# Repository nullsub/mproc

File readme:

MPROC is a cpu built out of 74xx logic-gates.

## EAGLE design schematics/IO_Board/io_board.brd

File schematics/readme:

eagle is used for the schematics

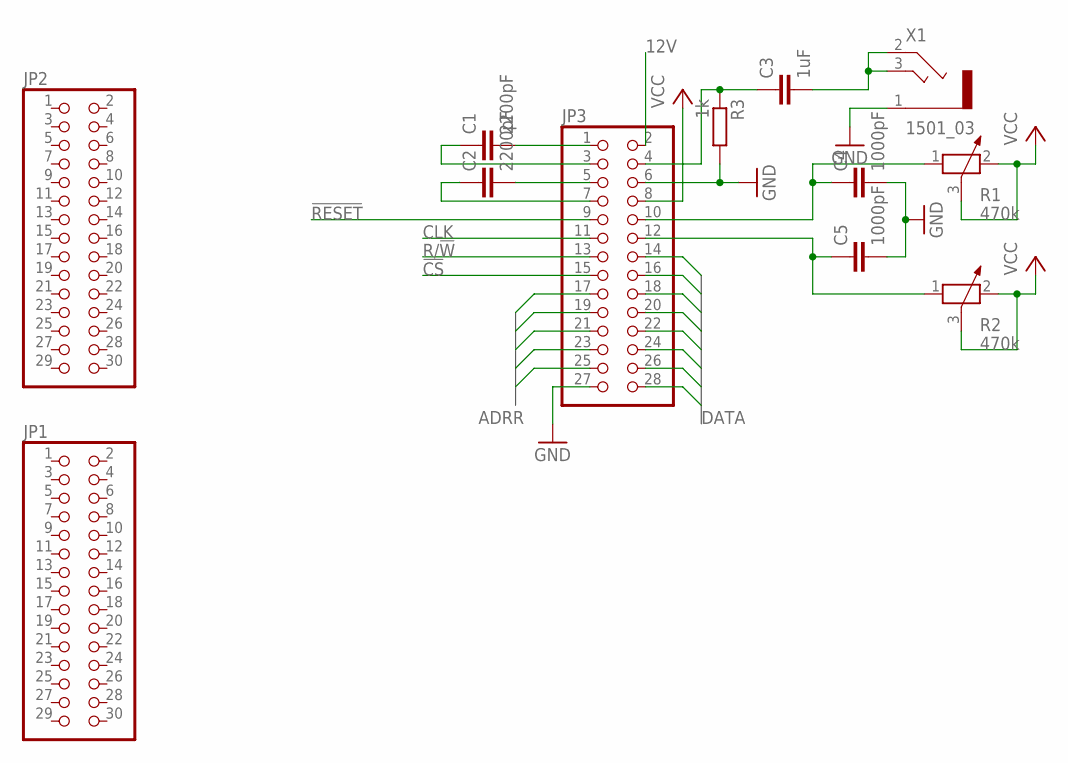
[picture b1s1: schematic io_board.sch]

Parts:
C1, C2: 2200pF; C1206
C3: 1uF; C1206
C4, C5: 1000pF; C1206
JP1, JP2: PINHD-2X15; 2X15
JP3: PINHD-2X14; 2X14
R1, R2: 470k; PT-10
R3: 1k; R0805
X1: 1501_03

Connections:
12V: JP3.2
!CS: JP3.15
!RESET: JP3.9
CLK: JP3.11
GND: C4.2, C5.2, JP3.6, JP3.27, R3.2, X1.1
unnamed: C4.1, JP3.10, R1.1
unnamed: C1.2, JP3.1
unnamed: C1.1, JP3.3
unnamed: C5.1, JP3.12, R2.1
unnamed: C2.2, JP3.5
unnamed: C2.1, JP3.7
unnamed: C3.2, X1.2, X1.3
unnamed: C3.1, JP3.4, R3.1
R/!W: JP3.13
VCC: JP3.8, R1.2, R1.3, R2.2, R2.3

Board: 2 copper layers, 12 parts (0 on the bottom side), 10 nets, no tracks yet.

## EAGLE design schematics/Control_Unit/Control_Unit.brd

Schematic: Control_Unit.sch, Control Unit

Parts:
IC1, IC8, IC48, IC49, IC55, IC56, IC65, IC68, IC70, IC71, IC94, IC96, IC112: 74HCT32N; DIL14
IC2, IC10, IC20, IC24, IC30, IC40, IC52, IC59, IC63, IC72, IC78, IC88, IC89, IC92, IC99, IC100, IC108, IC126, IC130: 74HCT08N; DIL14
IC3, IC4, IC15, IC16, IC22, IC23, IC31, IC32, IC37, IC38, IC42, IC43, IC46, IC47, IC50, IC51: 74HC151N; DIL16
IC5, IC18, IC26, IC33, IC41, IC45, IC73, IC79, IC81, IC85: 74HCT374N; DIL20
IC6, IC7, IC28, IC77, IC82, IC83, IC87, IC90, IC91, IC95: 74AC08N; DIL14
IC9: 74AC157N; DIL16
IC11, IC12, IC13, IC21, IC27, IC34: 74ACT157N; DIL16
IC14, IC67, IC86, IC129: 74HCT04N; DIL14
IC17, IC57, IC58, IC60, IC61, IC64, IC69, IC74, IC75, IC80, IC93, IC97, IC102, IC106: 74HC193N; DIL16
IC19, IC29, IC39, IC44: 74ACT02N; DIL14
IC25: 74AC86N; DIL14
IC35, IC36, IC101, IC103: 74HC373N; DIL20
IC53, IC54, IC105, IC131: 74HC74N; DIL14
JP1, JP2: PINHD-2X15; 2X15
JP3, JP4, JP5: PINHD-2X20; 2X20

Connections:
!CLR_CARRY_BIT: IC131.1 (CLR), JP4.12
!ENABLE_REG_OUTPUT: IC112.1 (I0), IC112.5 (I1), IC112.11 (O)
!IR_DATA_OUT_7: IC59.10 (I1), IC86.10 (O), IC99.10 (I1)
!OPCODE_5: IC14.6 (O), IC28.2 (I1), IC28.5 (I1)
!REGISTER_RESET: IC17.14 (CLR), IC57.14 (CLR), IC58.14 (CLR), IC60.14 (CLR), IC61.14 (CLR), IC64.14 (CLR), IC69.14 (CLR), IC74.14 (CLR), IC75.14 (CLR), IC80.14 (CLR), IC93.14 (CLR), IC97.14 (CLR), IC102.14 (CLR), IC106.14 (CLR), JP4.8
!RING_CNTR_RESET: IC53.4 (PRE), IC53.13 (CLR), IC54.1 (CLR), IC54.13 (CLR), IC105.1 (CLR), IC105.13 (CLR), JP4.10
!SET_CARRY_BIT: IC131.4 (PRE), JP4.14
!TWO_BYTE_CMD: IC14.11 (I), IC89.10 (I1), IC96.8 (O)
ADRR_0: IC13.4 (1Y), JP1.1
ADRR_1: IC13.7 (2Y), JP1.3
ADRR_2: IC13.9 (3Y), JP1.5
ADRR_3: IC13.12 (4Y), JP1.7
ADRR_4: IC21.4 (1Y), JP1.9
ADRR_5: IC21.7 (2Y), JP1.11
ADRR_6: IC21.9 (3Y), JP1.13
ADRR_7: IC21.12 (4Y), JP1.15
ADRR_8: IC27.4 (1Y), JP1.17
ADRR_9: IC27.7 (2Y), JP1.19
ADRR_10: IC27.9 (3Y), JP1.21
ADRR_11: IC27.12 (4Y), JP1.23
ADRR_12: IC34.4 (1Y), JP1.25
ADRR_13: IC34.7 (2Y), JP1.27
ADRR_14: IC34.9 (3Y), JP1.29
ADRR_15: IC34.12 (4Y), IC67.5 (I), IC68.9 (I0)
ALU_CARRY_BIT: IC78.12 (I0), IC89.4 (I0), IC131.5 (Q), JP4.16
ALU_CARRY_IN: IC89.6 (O), JP5.34
ALU_CARRY_OUT: IC72.5 (I1), IC99.9 (I0), IC131.2 (D), JP5.32
ALU_NR1_ENABLE_ALU: IC49.9 (I0), IC70.1 (I0), IC77.3 (O)
ALU_NR1_ENABLE_JMP_O: IC49.10 (I1), IC59.8 (O)
ALU_NR2_ENABLE_ALU: IC49.12 (I0), IC70.2 (I1), IC77.6 (O)
ALU_NR2_ENABLE_JMP_O: IC49.13 (I1), IC108.8 (O)
ALU_NR3_ENABLE_ALU: IC70.4 (I0), IC77.8 (O), JP5.26
ALU_NR4_ENABLE_ALU: IC70.5 (I1), IC77.11 (O), JP5.24
ALU_OUTPUT_ENABLE/FILL_PC_L_JMP_O: IC40.3 (O), IC49.2 (I1), IC56.12 (I0)
CARRY&&!IR_DATA: IC88.12 (I0), IC99.8 (O)
CARRY&&IR_DATA: IC72.6 (O), IC88.4 (I0)
CLR_NOT_CS/CLR_NOT_WE_PUSH: IC19.8 (I0), IC67.1 (I), IC126.6 (O)
CLR_NOT_OE/CLR_NOT_CS/PC_COUNT_UP_CYCL_2: IC53.9 (Q), IC55.4 (I0), IC55.12 (I0), JP4.28
CLR_NOT_OE/CLR_NOT_CS_POP/FILL_REGISTER_POP: IC19.9 (I1), IC96.4 (I0), IC100.6 (O), JP2.4
CLR_NOT_OE/PC_COUNT_UP/CLR_NOT_CS_CYCL_1: IC53.5 (Q), IC55.5 (I1), IC89.9 (I0), IC89.12 (I0), JP4.26
CYCLE1/CYLCE2: IC19.6 (I1), IC39.11 (I0), IC55.6 (O), IC68.4 (I0)
DATA0: IC5.3 (1D), IC17.15 (A), IC18.3 (1D), IC26.3 (1D), IC33.3 (1D), IC35.2 (1Q), IC36.2 (1Q), IC41.3 (1D), IC45.3 (1D), IC57.15 (A), IC60.15 (A), IC69.15 (A), IC73.3 (1D), IC79.3 (1D), IC81.3 (1D), IC85.3 (1D), IC101.2 (1Q), IC103.3 (1D), JP1.2, JP5.23
DATA1: IC5.4 (2D), IC17.1 (B), IC18.4 (2D), IC26.4 (2D), IC33.4 (2D), IC35.5 (2Q), IC36.5 (2Q), IC41.4 (2D), IC45.4 (2D), IC57.1 (B), IC60.1 (B), IC69.1 (B), IC73.4 (2D), IC79.4 (2D), IC81.4 (2D), IC85.4 (2D), IC101.5 (2Q), IC103.4 (2D), JP1.4, JP5.25
DATA2: IC5.7 (3D), IC17.10 (C), IC18.7 (3D), IC26.7 (3D), IC33.7 (3D), IC35.6 (3Q), IC36.6 (3Q), IC41.7 (3D), IC45.7 (3D), IC57.10 (C), IC60.10 (C), IC69.10 (C), IC73.7 (3D), IC79.7 (3D), IC81.7 (3D), IC85.7 (3D), IC101.6 (3Q), IC103.7 (3D), JP1.6, JP5.27
DATA3: IC5.8 (4D), IC17.9 (D), IC18.8 (4D), IC26.8 (4D), IC33.8 (4D), IC35.9 (4Q), IC36.9 (4Q), IC41.8 (4D), IC45.8 (4D), IC57.9 (D), IC60.9 (D), IC69.9 (D), IC73.8 (4D), IC79.8 (4D), IC81.8 (4D), IC85.8 (4D), IC101.9 (4Q), IC103.8 (4D), JP1.8, JP5.29
DATA4: IC5.13 (5D), IC18.13 (5D), IC26.13 (5D), IC33.13 (5D), IC35.12 (5Q), IC36.12 (5Q), IC41.13 (5D), IC45.13 (5D), IC58.15 (A), IC61.15 (A), IC64.15 (A), IC73.13 (5D), IC74.15 (A), IC79.13 (5D), IC81.13 (5D), IC85.13 (5D), IC101.12 (5Q), IC103.13 (5D), JP1.10, JP5.31
DATA5: IC5.14 (6D), IC18.14 (6D), IC26.14 (6D), IC33.14 (6D), IC35.15 (6Q), IC36.15 (6Q), IC41.14 (6D), IC45.14 (6D), IC58.1 (B), IC61.1 (B), IC64.1 (B), IC73.14 (6D), IC74.1 (B), IC79.14 (6D), IC81.14 (6D), IC85.14 (6D), IC101.15 (6Q), IC103.14 (6D), JP1.12, JP5.33
DATA6: IC5.17 (7D), IC18.17 (7D), IC26.17 (7D), IC33.17 (7D), IC35.16 (7Q), IC36.16 (7Q), IC41.17 (7D), IC45.17 (7D), IC58.10 (C), IC61.10 (C), IC64.10 (C), IC73.17 (7D), IC74.10 (C), IC79.17 (7D), IC81.17 (7D), IC85.17 (7D), IC101.16 (7Q), IC103.17 (7D), JP1.14, JP5.35
DATA7: IC5.18 (8D), IC18.18 (8D), IC26.18 (8D), IC33.18 (8D), IC35.19 (8Q), IC36.19 (8Q), IC41.18 (8D), IC45.18 (8D), IC58.9 (D), IC61.9 (D), IC64.9 (D), IC73.18 (8D), IC74.9 (D), IC79.18 (8D), IC81.18 (8D), IC85.18 (8D), IC101.19 (8Q), IC103.18 (8D), JP1.16, JP5.37
DATA_BUS_ENABLE_LATCH: IC35.11 (ENC), IC59.3 (O)
DBUS_SELECTOR_TABLE_2: IC11.1 (!A!/B), IC55.8 (O)
ENABLE_ALU_OUTPUT: IC49.3 (O), IC67.11 (I), IC112.13 (I1)
ENABLE_ALU_OUTPUT/FILL_REGISTER_ALU: IC49.1 (I0), IC72.11 (O), IC112.10 (I1)
FDSGDFGFDSGFSDGFDGSDG: IC8.10 (I1), IC8.13 (I1), IC19.1 (O)
FILL_LR_H/COUNT_PC_DOWN_SAVE_LR: IC44.11 (I0), IC126.11 (O), IC129.9 (I)
FILL_LR_L/WRITE_PC_H_DBUS_SAVE_LR: IC44.8 (I0), IC65.13 (I1), IC92.6 (O)
FILL_PC_H_RET: IC56.4 (I0), IC126.3 (O)
FILL_PC_L/WRITE_LR_H_DBUS_RET: IC56.10 (I1), IC65.2 (I1), IC65.4 (I0), IC100.3 (O)
FILL_PTR_H_SET_PTR: IC39.6 (I1), IC88.8 (O)
FILL_PTR_L/WRITE_REGB_TO_DBUS_SET_PTR: IC1.13 (I1), IC39.3 (I1), IC92.3 (O)
FILL_REGISTER_MOV: IC108.3 (O), IC112.9 (I0)
FSDFAFSDFSFDDDDDDDDDDDDDDDDDDDDDDDDDDDDDDDD1: IC2.2 (I1), IC2.10 (I1), IC10.2 (I1), IC10.10 (I1), IC20.6 (O)
GND: IC1.7 (GND), IC2.7 (GND), IC3.7 (G), IC3.8 (GND), IC4.7 (G), IC4.8 (GND), IC5.1 (OC), IC5.10 (GND), IC6.7 (GND), IC7.7 (GND), IC8.7 (GND), IC9.8 (GND), IC9.15 (G), IC10.7 (GND), IC11.8 (GND), IC11.14 (4A), IC11.15 (G), IC12.3 (1B), IC12.8 (GND), IC12.15 (G), IC13.8 (GND), IC13.15 (G), IC14.7 (GND), IC15.7 (G), IC15.8 (GND), IC16.7 (G), IC16.8 (GND), IC17.8 (GND), IC18.1 (OC), IC18.10 (GND), IC19.7 (GND), IC20.7 (GND), IC21.8 (GND), IC21.15 (G), IC22.7 (G), IC22.8 (GND), IC23.7 (G), IC23.8 (GND), IC24.7 (GND), IC25.7 (GND), IC26.1 (OC), IC26.10 (GND), IC27.8 (GND), IC27.15 (G), IC28.7 (GND), IC29.7 (GND), IC30.7 (GND), IC31.7 (G), IC31.8 (GND), IC32.7 (G), IC32.8 (GND), IC33.1 (OC), IC33.10 (GND), IC34.8 (GND), IC34.15 (G), IC35.10 (GND), IC36.10 (GND), IC37.7 (G), IC37.8 (GND), IC38.7 (G), IC38.8 (GND), IC39.7 (GND), IC40.7 (GND), IC41.1 (OC), IC41.10 (GND), IC42.7 (G), IC42.8 (GND), IC43.7 (G), IC43.8 (GND), IC44.7 (GND), IC45.1 (OC), IC45.10 (GND), IC46.7 (G), IC46.8 (GND), IC47.7 (G), IC47.8 (GND), IC48.7 (GND), IC49.7 (GND), IC50.7 (G), IC50.8 (GND), IC51.7 (G), IC51.8 (GND), IC52.7 (GND), IC53.7 (GND), IC54.7 (GND), IC55.7 (GND), IC56.7 (GND), IC57.8 (GND), IC58.8 (GND), IC59.7 (GND), IC60.8 (GND), IC61.8 (GND), IC63.7 (GND), IC64.8 (GND), IC65.7 (GND), IC67.7 (GND), IC68.7 (GND), IC69.8 (GND), IC70.7 (GND), IC71.7 (GND), IC72.7 (GND), IC73.1 (OC), IC73.10 (GND), IC74.8 (GND), IC75.1 (B), IC75.8 (GND), IC75.9 (D), IC75.10 (C), IC75.15 (A), IC77.7 (GND), IC78.7 (GND), IC79.1 (OC), IC79.10 (GND), IC80.1 (B), IC80.8 (GND), IC80.9 (D), IC80.10 (C), IC80.15 (A), IC81.1 (OC), IC81.10 (GND), IC82.7 (GND), IC83.7 (GND), IC85.1 (OC), IC85.10 (GND), IC86.7 (GND), IC87.7 (GND), IC88.7 (GND), IC89.7 (GND), IC90.7 (GND), IC91.7 (GND), IC92.7 (GND), IC93.1 (B), IC93.8 (GND), IC93.9 (D), IC93.10 (C), IC93.15 (A), IC94.7 (GND), IC95.7 (GND), IC96.7 (GND), IC97.1 (B), IC97.8 (GND), IC97.9 (D), IC97.10 (C), IC97.15 (A), IC99.7 (GND), IC100.7 (GND), IC101.10 (GND), IC102.1 (B), IC102.8 (GND), IC102.9 (D), IC102.10 (C), IC102.15 (A), IC103.1 (OC), IC103.10 (GND), IC105.7 (GND), IC106.1 (B), IC106.8 (GND), IC106.9 (D), IC106.10 (C), IC106.15 (A), IC108.7 (GND), IC112.7 (GND), IC126.7 (GND), IC129.7 (GND), IC130.7 (GND), IC131.7 (GND), JP1.18, JP1.26, JP1.30, JP2.2, JP2.10, JP2.14, JP2.18, JP2.26, JP2.30, JP3.17, JP3.18, JP3.21, JP3.22, JP3.39, JP3.40, JP4.1, JP4.2, JP4.5, JP4.6, JP4.7, JP4.9, JP4.11, JP4.13, JP4.15, JP4.21, JP4.22, JP4.24, JP4.38, JP4.39, JP4.40, JP5.17, JP5.18, JP5.21, JP5.22, JP5.36, JP5.38, JP5.39, JP5.40
INPUT_REG0/OPC4/5_IS_NULL: IC2.1 (I0), IC2.4 (I0), IC9.3 (1B), IC24.1 (I0), IC24.4 (I0), IC28.3 (O), IC30.1 (I0), IC88.1 (I0), IC99.13 (I1)
INPUT_REG1: IC2.9 (I0), IC2.12 (I0), IC9.6 (2B), IC24.9 (I0), IC24.12 (I0), IC28.6 (O), IC30.4 (I0)
INPUT_REG2/OPC_4/5==11: IC9.10 (3B), IC10.1 (I0), IC10.4 (I0), IC28.8 (O), IC30.9 (I0), IC63.4 (I0), IC63.12 (I0)
INPUT_REG3: IC9.13 (4B), IC10.9 (I0), IC10.12 (I0), IC28.11 (O), IC30.12 (I0)
INPUT_REG_IS_NOT_OUTPUT_REG: IC6.1 (I0), IC6.4 (I0), IC6.9 (I0), IC6.12 (I0), IC19.3 (I1), IC71.6 (O), IC96.9 (I0)
IO_INPUT1_0: IC3.12 (D7), JP3.2
IO_INPUT1_1: IC15.12 (D7), JP3.4
IO_INPUT1_2: IC22.12 (D7), JP3.6
IO_INPUT1_3: IC31.12 (D7), JP3.8
IO_INPUT1_4: IC37.12 (D7), JP3.10
IO_INPUT1_5: IC42.12 (D7), JP3.12
IO_INPUT1_6: IC46.12 (D7), JP3.14
IO_INPUT1_7: IC50.12 (D7), JP3.16
IO_INPUT2_0: IC4.15 (D4), JP3.24
IO_INPUT2_1: IC16.15 (D4), JP3.26
IO_INPUT2_2: IC23.15 (D4), JP3.28
IO_INPUT2_3: IC32.15 (D4), JP3.30
IO_INPUT2_4: IC38.15 (D4), JP3.32
IO_INPUT2_5: IC43.15 (D4), JP3.34
IO_INPUT2_6: IC47.15 (D4), JP3.36
IO_INPUT2_7: IC51.15 (D4), JP3.38
IO_OUTPUT1_0: IC4.14 (D5), IC73.2 (1Q), JP3.1
IO_OUTPUT1_1: IC16.14 (D5), IC73.5 (2Q), JP3.3
IO_OUTPUT1_2: IC23.14 (D5), IC73.6 (3Q), JP3.5
IO_OUTPUT1_3: IC32.14 (D5), IC73.9 (4Q), JP3.7
IO_OUTPUT1_4: IC38.14 (D5), IC73.12 (5Q), JP3.9
IO_OUTPUT1_5: IC43.14 (D5), IC73.15 (6Q), JP3.11
IO_OUTPUT1_6: IC47.14 (D5), IC73.16 (7Q), JP3.13
IO_OUTPUT1_7: IC51.14 (D5), IC73.19 (8Q), JP3.15
IO_OUTPUT2_0: IC4.13 (D6), IC79.2 (1Q), JP3.23
IO_OUTPUT2_1: IC16.13 (D6), IC79.5 (2Q), JP3.25
IO_OUTPUT2_2: IC23.13 (D6), IC79.6 (3Q), JP3.27
IO_OUTPUT2_3: IC32.13 (D6), IC79.9 (4Q), JP3.29
IO_OUTPUT2_4: IC38.13 (D6), IC79.12 (5Q), JP3.31
IO_OUTPUT2_5: IC43.13 (D6), IC79.15 (6Q), JP3.33
IO_OUTPUT2_6: IC47.13 (D6), IC79.16 (7Q), JP3.35
IO_OUTPUT2_7: IC51.13 (D6), IC79.19 (8Q), JP3.37
IO_OUTPUT_REG_1_LOAD_INPUT: IC10.8 (O), IC73.11 (CLK)
IO_OUTPUT_REG_2_LOAD_INPUT: IC10.11 (O), IC79.11 (CLK)
IR_DATA_OUT_0: IC3.4 (D0), IC41.2 (1Q)
IR_DATA_OUT_1: IC15.4 (D0), IC41.5 (2Q)
IR_DATA_OUT_2: IC22.4 (D0), IC41.6 (3Q)
IR_DATA_OUT_3: IC31.4 (D0), IC41.9 (4Q)
IR_DATA_OUT_4: IC37.4 (D0), IC41.12 (5Q)
IR_DATA_OUT_5: IC41.15 (6Q), IC42.4 (D0)
IR_DATA_OUT_6: IC41.16 (7Q), IC46.4 (D0)
IR_DATA_OUT_7: IC41.19 (8Q), IC50.4 (D0), IC72.4 (I0), IC86.11 (I), IC108.10 (I1)
IR_LOAD_INPUT/!CYCL_2: IC41.11 (CLK), IC53.8 (!Q)
LATCH_ALU_INPUT_ALU_JMP_O: IC1.3 (O), IC1.4 (I0), IC103.11 (ENC)
LATCH_ALU_INPUT_B/WRITE_REGB_TO_DBUS_ALU: IC1.1 (I0), IC72.3 (O)
LATCH_ALU_INPUT_B/WRITE_REGB_TO_DBUS_JMP_O: IC1.2 (I1), IC40.6 (O)
LDR: IC1.10 (I1), IC91.11 (O)
LDR/LDR_I: IC1.8 (O), IC48.1 (I0), IC100.10 (I1)
LDR_I: IC1.9 (I0), IC89.2 (I1), IC91.8 (O)
LR_DATA_OUT_0: IC4.4 (D0), IC81.2 (1Q)
LR_DATA_OUT_1: IC16.4 (D0), IC81.5 (2Q)
LR_DATA_OUT_2: IC23.4 (D0), IC81.6 (3Q)
LR_DATA_OUT_3: IC32.4 (D0), IC81.9 (4Q)
LR_DATA_OUT_4: IC38.4 (D0), IC81.12 (5Q)
LR_DATA_OUT_5: IC43.4 (D0), IC81.15 (6Q)
LR_DATA_OUT_6: IC47.4 (D0), IC81.16 (7Q)
LR_DATA_OUT_7: IC51.4 (D0), IC81.19 (8Q)
LR_DATA_OUT_8: IC4.3 (D1), IC85.2 (1Q)
LR_DATA_OUT_9: IC16.3 (D1), IC85.5 (2Q)
LR_DATA_OUT_10: IC23.3 (D1), IC85.6 (3Q)
LR_DATA_OUT_11: IC32.3 (D1), IC85.9 (4Q)
LR_DATA_OUT_12: IC38.3 (D1), IC85.12 (5Q)
LR_DATA_OUT_13: IC43.3 (D1), IC85.15 (6Q)
LR_DATA_OUT_14: IC47.3 (D1), IC85.16 (7Q)
LR_DATA_OUT_15: IC51.3 (D1), IC85.19 (8Q)
LR_H_LOAD_INPUT_NOT: IC44.13 (O), IC85.11 (CLK)
LR_H_LOAD_INPUT_TABLE_1: IC24.6 (O), IC44.12 (I1)
LR_L_LOAD_INPUT_NOT: IC44.10 (O), IC81.11 (CLK)
LR_L_LOAD_INPUT_TABLE_1: IC24.3 (O), IC44.9 (I1)
MEM_NOT_CE: IC19.4 (O), IC68.10 (I1), IC68.13 (I1)
MEM_NOT_OE: IC67.12 (O), JP1.20, JP2.20
MEM_NOT_WE: IC67.4 (O), JP1.24, JP2.24
MEM_OE: IC67.13 (I), IC68.6 (O), IC112.12 (I0)
unnamed: IC3.5 (Y), IC35.3 (1D)
unnamed: IC99.11 (O), IC129.11 (I)
unnamed: IC15.5 (Y), IC35.4 (2D)
unnamed: IC1.5 (I1), IC1.11 (O)
unnamed: IC55.13 (I1), IC89.8 (O)
unnamed: IC30.2 (I1), IC30.5 (I1), IC30.10 (I1), IC30.13 (I1), IC112.8 (O)
unnamed: IC59.1 (I0), IC129.4 (O)
unnamed: IC70.13 (I1), IC78.3 (O)
unnamed: IC29.3 (I1), IC30.3 (O)
unnamed: IC86.2 (O), IC87.1 (I0), IC87.12 (I0)
unnamed: IC55.3 (O), IC129.13 (I)
unnamed: IC36.11 (ENC), IC59.11 (O)
unnamed: IC48.11 (O), IC92.12 (I0)
unnamed: IC39.12 (I1), IC48.6 (O)
unnamed: IC52.5 (I1), IC52.10 (I1), IC52.13 (I1), IC108.11 (O)
unnamed: IC86.4 (O), IC87.2 (I1), IC87.5 (I1)
unnamed: IC63.3 (O), IC100.5 (I1), IC130.13 (I1)
unnamed: IC53.12 (D), IC89.11 (O)
unnamed: IC82.2 (I1), IC82.4 (I0), IC87.3 (O)
unnamed: IC39.9 (I1), IC94.6 (O)
unnamed: IC48.8 (O), IC48.13 (I1), IC99.12 (I0)
unnamed: IC86.13 (I), IC88.3 (O), IC108.5 (I1)
unnamed: IC22.5 (Y), IC35.7 (3D)
unnamed: IC6.11 (O), IC9.14 (4A)
unnamed: IC82.10 (I1), IC82.12 (I0), IC87.6 (O)
unnamed: IC87.8 (O), IC90.1 (I0), IC90.4 (I0)
unnamed: IC6.8 (O), IC9.11 (3A)
unnamed: IC87.11 (O), IC90.9 (I0), IC90.12 (I0)
unnamed: IC82.1 (I0), IC82.9 (I0), IC86.6 (O), IC90.2 (I1), IC90.10 (I1)
unnamed: IC8.11 (O), IC11.11 (3A)
unnamed: IC68.11 (O), JP2.22
unnamed: IC17.13 (BO), IC61.4 (DN)
unnamed: IC71.13 (I1), IC83.11 (O)
unnamed: IC77.1 (I0), IC77.4 (I0), IC82.3 (O)
unnamed: IC77.9 (I0), IC77.12 (I0), IC82.6 (O)
unnamed: IC82.8 (O), IC83.1 (I0), IC83.4 (I0)
unnamed: IC82.11 (O), IC83.9 (I0), IC83.12 (I0)
unnamed: IC90.3 (O), IC91.1 (I0), IC91.4 (I0)
unnamed: IC90.6 (O), IC91.9 (I0), IC91.12 (I0)
unnamed: IC90.8 (O), IC95.1 (I0), IC95.4 (I0)
unnamed: IC90.11 (O), IC95.9 (I0), IC95.13 (I1)
unnamed: IC77.5 (I1), IC77.13 (I1), IC83.5 (I1), IC83.13 (I1), IC86.8 (O), IC91.5 (I1), IC91.13 (I1), IC95.5 (I1), IC95.12 (I0)
unnamed: IC36.1 (OC), IC112.3 (O)
unnamed: IC92.11 (O), IC96.10 (I1)
unnamed: IC31.5 (Y), IC35.8 (4D)
unnamed: IC25.6 (O), IC71.4 (I0)
unnamed: IC70.6 (O), IC70.10 (I1)
unnamed: IC70.3 (O), IC70.9 (I0)
unnamed: IC25.3 (O), IC71.5 (I1)
unnamed: IC129.6 (O), IC131.11 (CLK)
unnamed: IC20.2 (I1), IC20.5 (I1), IC20.10 (I1), IC20.13 (I1), IC96.6 (O)
unnamed: IC8.8 (O), IC11.2 (1A)
unnamed: IC70.11 (O), IC108.2 (I1)
unnamed: IC54.2 (D), IC55.11 (O)
unnamed: IC29.6 (I1), IC30.6 (O)
unnamed: IC101.7 (3D), JP5.6
unnamed: IC101.4 (2D), JP5.4
unnamed: IC101.3 (1D), JP5.2
unnamed: IC101.17 (7D), JP5.14
unnamed: IC101.14 (6D), JP5.12
unnamed: IC101.13 (5D), JP5.10
unnamed: IC29.9 (I1), IC30.8 (O)
unnamed: IC35.13 (5D), IC37.5 (Y)
unnamed: IC101.8 (4D), JP5.8
unnamed: IC67.6 (O), IC68.12 (I0)
unnamed: IC8.3 (O), IC8.9 (I0)
unnamed: IC6.6 (O), IC9.5 (2A)
unnamed: IC68.8 (O), JP1.22
unnamed: IC29.12 (I1), IC30.11 (O)
unnamed: IC6.3 (O), IC9.2 (1A)
unnamed: IC8.6 (O), IC11.5 (2A)
unnamed: IC67.8 (O), IC131.3 (CLK)
unnamed: IC35.14 (6D), IC42.5 (Y)
unnamed: IC35.17 (7D), IC46.5 (Y)
unnamed: IC75.12 (CO), IC80.5 (UP)
unnamed: IC35.18 (8D), IC50.5 (Y)
unnamed: IC17.12 (CO), IC61.5 (UP)
unnamed: IC48.3 (O), IC48.12 (I0)
unnamed: IC71.8 (O), IC108.4 (I0), IC108.12 (I0)
unnamed: IC112.4 (I0), IC131.9 (Q)
unnamed: IC57.4 (DN), IC129.8 (O)
unnamed: IC112.2 (I1), IC131.8 (!Q)
unnamed: IC67.10 (O), IC101.1 (OC)
unnamed: IC61.13 (BO), IC69.4 (DN)
unnamed: IC61.12 (CO), IC69.5 (UP)
unnamed: IC88.10 (I1), IC91.6 (O), IC92.2 (I1)
unnamed: IC8.12 (I0), IC9.12 (4Y)
unnamed: IC8.4 (I0), IC9.7 (2Y)
unnamed: IC8.2 (I1), IC8.5 (I1), IC9.9 (3Y)
unnamed: IC69.13 (BO), IC74.4 (DN)
unnamed: IC69.12 (CO), IC74.5 (UP)
unnamed: IC8.1 (I0), IC9.4 (1Y)
unnamed: IC19.13 (O), IC63.2 (I1)
unnamed: IC78.5 (I1), IC83.8 (O)
unnamed: IC70.12 (I0), IC83.3 (O)
unnamed: IC78.2 (I1), IC83.6 (O)
unnamed: IC71.12 (I0), IC78.6 (O)
unnamed: IC103.2 (1Q), JP5.1
unnamed: IC103.5 (2Q), JP5.3
unnamed: IC2.5 (I1), IC2.13 (I1), IC10.5 (I1), IC10.13 (I1), IC20.3 (O)
unnamed: IC25.8 (O), IC60.5 (UP)
unnamed: IC25.9 (I0), IC58.12 (CO)
unnamed: IC49.11 (O), JP5.28
unnamed: IC86.12 (O), IC108.13 (I1)
unnamed: IC44.3 (I1), IC56.11 (O)
unnamed: IC103.6 (3Q), JP5.5
unnamed: IC12.6 (2B), IC65.6 (O)
unnamed: IC103.9 (4Q), JP5.7
unnamed: IC103.12 (5Q), JP5.9
unnamed: IC103.15 (6Q), JP5.11
unnamed: IC103.16 (7Q), JP5.13
unnamed: IC103.19 (8Q), JP5.15
unnamed: IC94.5 (I1), IC94.11 (O)
unnamed: IC94.4 (I0), IC94.8 (O)
unnamed: IC94.2 (I1), IC96.11 (O)
unnamed: IC94.1 (I0), IC96.3 (O)
unnamed: IC39.8 (I0), IC94.3 (O)
unnamed: IC52.2 (I1), IC59.6 (O), IC78.10 (I1), IC92.5 (I1), IC126.13 (I1)
unnamed: IC71.9 (I0), IC71.11 (O)
unnamed: IC71.10 (I1), IC78.11 (O)
unnamed: IC78.13 (I1), IC91.3 (O)
unnamed: IC49.8 (O), JP5.30
unnamed: IC92.13 (I1), IC129.10 (O)
unnamed: IC97.12 (CO), IC102.5 (UP)
unnamed: IC93.12 (CO), IC97.5 (UP)
unnamed: IC93.13 (BO), IC97.4 (DN)
unnamed: IC97.13 (BO), IC102.4 (DN)
unnamed: IC7.1 (I0), IC7.12 (I0), IC14.12 (O)
unnamed: IC7.2 (I1), IC7.5 (I1), IC14.2 (O)
unnamed: IC102.13 (BO), IC106.4 (DN)
unnamed: IC102.12 (CO), IC106.5 (UP)
unnamed: IC92.8 (O), IC99.2 (I1), IC100.2 (I1), IC126.2 (I1), IC126.10 (I1)
unnamed: IC14.4 (O), IC28.1 (I0), IC28.12 (I0)
unnamed: IC101.18 (8D), JP5.16
unnamed: IC20.11 (O), IC24.5 (I1), IC24.13 (I1)
unnamed: IC67.2 (O), JP2.8
unnamed: IC19.10 (O), JP2.6
unnamed: IC20.8 (O), IC24.2 (I1), IC24.10 (I1)
unnamed: IC57.12 (CO), IC58.5 (UP)
unnamed: IC60.13 (BO), IC64.4 (DN)
unnamed: IC60.12 (CO), IC64.5 (UP)
unnamed: IC65.3 (O), IC65.9 (I0)
unnamed: IC4.5 (Y), IC36.3 (1D)
unnamed: IC16.5 (Y), IC36.4 (2D)
unnamed: IC23.5 (Y), IC36.7 (3D)
unnamed: IC32.5 (Y), IC36.8 (4D)
unnamed: IC36.13 (5D), IC38.5 (Y)
unnamed: IC36.14 (6D), IC43.5 (Y)
unnamed: IC36.17 (7D), IC47.5 (Y)
unnamed: IC36.18 (8D), IC51.5 (Y)
OPC==E: IC19.12 (I1), IC63.11 (O), IC92.10 (I1)
OPC==F: IC19.11 (I0), IC59.4 (I0), IC63.6 (O)
OPCODE_0: IC45.2 (1Q), IC86.1 (I), IC87.4 (I0), IC87.9 (I0)
OPCODE_1: IC45.5 (2Q), IC86.3 (I), IC87.10 (I1), IC87.13 (I1)
OPCODE_2: IC45.6 (3Q), IC82.5 (I1), IC82.13 (I1), IC86.5 (I), IC90.5 (I1), IC90.13 (I1)
OPCODE_3: IC45.9 (4Q), IC77.2 (I1), IC77.10 (I1), IC83.2 (I1), IC83.10 (I1), IC86.9 (I), IC91.2 (I1), IC91.10 (I1), IC95.2 (I1), IC95.10 (I1)
OPCODE_4: IC11.3 (1B), IC14.3 (I), IC25.4 (I0), IC28.4 (I0), IC28.9 (I0), IC45.12 (5Q)
OPCODE_5: IC11.6 (2B), IC14.5 (I), IC25.1 (I0), IC28.10 (I1), IC28.13 (I1), IC45.15 (6Q)
OPCODE_6: IC7.4 (I0), IC7.9 (I0), IC11.10 (3B), IC14.13 (I), IC25.5 (I1), IC45.16 (7Q)
OPCODE_7: IC7.10 (I1), IC7.13 (I1), IC11.13 (4B), IC14.1 (I), IC25.2 (I1), IC45.19 (8Q)
OPCODE_LOAD_INPUT/!CYCL_1: IC45.11 (CLK), IC53.6 (!Q)
OPC_67_OUPUT0/REG0_JMP: IC6.2 (I1), IC7.3 (O), IC20.1 (I0), IC88.2 (I1)
OPC_67_OUPUT1: IC6.5 (I1), IC7.6 (O), IC20.4 (I0)
OPC_67_OUPUT2==11: IC6.10 (I1), IC7.8 (O), IC20.9 (I0), IC63.5 (I1)
OPC_67_OUPUT3==10: IC6.13 (I1), IC7.11 (O), IC20.12 (I0), IC63.13 (I1)
OPERAND_REGB_OUTPUT: IC1.6 (O), IC9.1 (!A!/B), IC19.2 (I0)
PC_COUNT_UP: IC39.13 (O), IC57.5 (UP)
PC_COUNT_UP_RET: IC48.4 (I0), IC126.8 (O)
PC_COUNT_UP_SAVE_LR: IC48.5 (I1), IC52.3 (O)
PC_DATA_OUT_0: IC4.2 (D2), IC13.3 (1B), IC57.3 (QA)
PC_DATA_OUT_1: IC13.6 (2B), IC16.2 (D2), IC57.2 (QB)
PC_DATA_OUT_2: IC13.10 (3B), IC23.2 (D2), IC57.6 (QC)
PC_DATA_OUT_3: IC13.13 (4B), IC32.2 (D2), IC57.7 (QD)
PC_DATA_OUT_4: IC21.3 (1B), IC38.2 (D2), IC58.3 (QA)
PC_DATA_OUT_5: IC21.6 (2B), IC43.2 (D2), IC58.2 (QB)
PC_DATA_OUT_6: IC21.10 (3B), IC47.2 (D2), IC58.6 (QC)
PC_DATA_OUT_7: IC21.13 (4B), IC51.2 (D2), IC58.7 (QD)
PC_DATA_OUT_8: IC4.1 (D3), IC27.3 (1B), IC60.3 (QA)
PC_DATA_OUT_9: IC16.1 (D3), IC27.6 (2B), IC60.2 (QB)
PC_DATA_OUT_10: IC23.1 (D3), IC27.10 (3B), IC60.6 (QC)
PC_DATA_OUT_11: IC27.13 (4B), IC32.1 (D3), IC60.7 (QD)
PC_DATA_OUT_12: IC34.3 (1B), IC38.1 (D3), IC64.3 (QA)
PC_DATA_OUT_13: IC34.6 (2B), IC43.1 (D3), IC64.2 (QB)
PC_DATA_OUT_14: IC34.10 (3B), IC47.1 (D3), IC64.6 (QC)
PC_DATA_OUT_15: IC34.13 (4B), IC51.1 (D3), IC64.7 (QD)
PC_HIGH_LOAD_INPUT_JMP: IC52.8 (O), IC56.5 (I1)
PC_HIGH_LOAD_INPUT_NOT: IC44.4 (O), IC60.11 (LD), IC64.11 (LD)
PC_H_COUNT_DOWN_JMP_O: IC60.4 (DN), IC88.6 (O)
PC_H_COUNT_UP_JMP_O: IC25.10 (I1), IC88.11 (O)
PC_H_LOAD_INPUT_TABLE_1: IC24.11 (O), IC44.5 (I0)
PC_LOW_LOAD_INPUT_JMP: IC52.6 (O), IC56.9 (I0)
PC_LOW_LOAD_INPUT_NOT: IC44.1 (O), IC57.11 (LD), IC58.11 (LD)
PC_L_LOAD_INPUT_TABLE_1: IC24.8 (O), IC56.13 (I1)
PC_L_TO_DBUS: IC56.3 (O), IC65.5 (I1), IC65.12 (I0)
POP/SAVE_LR/RET: IC48.2 (I1), IC59.5 (I1), IC63.1 (I0), IC92.9 (I0), IC95.11 (O)
PTR_COUNT_UP: IC17.5 (UP), IC129.12 (O)
PTR_COUNT_UP_LDR_I: IC55.1 (I0), IC89.3 (O)
PTR_COUNT_UP_STR_I: IC55.2 (I1), IC99.6 (O)
PTR_DATA_OUT_0: IC3.14 (D5), IC13.2 (1A), IC17.3 (QA)
PTR_DATA_OUT_1: IC13.5 (2A), IC15.14 (D5), IC17.2 (QB)
PTR_DATA_OUT_2: IC13.11 (3A), IC17.6 (QC), IC22.14 (D5)
PTR_DATA_OUT_3: IC13.14 (4A), IC17.7 (QD), IC31.14 (D5)
PTR_DATA_OUT_4: IC21.2 (1A), IC37.14 (D5), IC61.3 (QA)
PTR_DATA_OUT_5: IC21.5 (2A), IC42.14 (D5), IC61.2 (QB)
PTR_DATA_OUT_6: IC21.11 (3A), IC46.14 (D5), IC61.6 (QC)
PTR_DATA_OUT_7: IC21.14 (4A), IC50.14 (D5), IC61.7 (QD)
PTR_DATA_OUT_8: IC3.13 (D6), IC27.2 (1A), IC69.3 (QA)
PTR_DATA_OUT_9: IC15.13 (D6), IC27.5 (2A), IC69.2 (QB)
PTR_DATA_OUT_10: IC22.13 (D6), IC27.11 (3A), IC69.6 (QC)
PTR_DATA_OUT_11: IC27.14 (4A), IC31.13 (D6), IC69.7 (QD)
PTR_DATA_OUT_12: IC34.2 (1A), IC37.13 (D6), IC74.3 (QA)
PTR_DATA_OUT_13: IC34.5 (2A), IC42.13 (D6), IC74.2 (QB)
PTR_DATA_OUT_14: IC34.11 (3A), IC46.13 (D6), IC74.6 (QC)
PTR_DATA_OUT_15: IC34.14 (4A), IC50.13 (D6), IC74.7 (QD)
PTR_H_LOAD_INPUT_NOT: IC39.4 (O), IC69.11 (LD), IC74.11 (LD)
PTR_L_LOAD_INPUT_NOT: IC17.11 (LD), IC39.1 (O), IC61.11 (LD)
PTR_TO_ABUS: IC13.1 (!A!/B), IC19.5 (I0), IC21.1 (!A!/B), IC27.1 (!A!/B), IC34.1 (!A!/B), IC68.3 (O)
PUSH: IC48.10 (I1), IC95.8 (O), IC126.5 (I1), IC130.5 (I1)
REG0_ZERO: IC39.10 (O), IC78.1 (I0), IC78.4 (I0), JP4.20
REGISTER_OUTPUT_SEL_0: IC3.11 (A), IC4.11 (A), IC12.4 (1Y), IC15.11 (A), IC16.11 (A), IC22.11 (A), IC23.11 (A), IC31.11 (A), IC32.11 (A), IC37.11 (A), IC38.11 (A), IC42.11 (A), IC43.11 (A), IC46.11 (A), IC47.11 (A), IC50.11 (A), IC51.11 (A)
REGISTER_OUTPUT_SEL_0_: IC11.4 (1Y), IC12.2 (1A)
REGISTER_OUTPUT_SEL_1: IC3.10 (B), IC4.10 (B), IC12.7 (2Y), IC15.10 (B), IC16.10 (B), IC22.10 (B), IC23.10 (B), IC31.10 (B), IC32.10 (B), IC37.10 (B), IC38.10 (B), IC42.10 (B), IC43.10 (B), IC46.10 (B), IC47.10 (B), IC50.10 (B), IC51.10 (B)
REGISTER_OUTPUT_SEL_1_: IC11.7 (2Y), IC12.5 (2A)
REGISTER_OUTPUT_SEL_2: IC3.9 (C), IC4.9 (C), IC12.9 (3Y), IC15.9 (C), IC16.9 (C), IC22.9 (C), IC23.9 (C), IC31.9 (C), IC32.9 (C), IC37.9 (C), IC38.9 (C), IC42.9 (C), IC43.9 (C), IC46.9 (C), IC47.9 (C), IC50.9 (C), IC51.9 (C)
REGISTER_OUTPUT_SEL_2_: IC11.9 (3Y), IC12.11 (3A)
REGISTER_OUTPUT_SEL_3: IC12.12 (4Y), IC59.12 (I0), IC129.3 (I), IC131.12 (D)
REGISTER_OUTPUT_SEL_3_: IC11.12 (4Y), IC12.14 (4A)
REGS_OUTPUT_TO_DATABUS_ENABLE: IC35.1 (OC), IC112.6 (O)
REG_0_LOAD_INPUT: IC29.1 (O), IC33.11 (CLK)
REG_0_OUT_0: IC3.3 (D1), IC33.2 (1Q), IC96.1 (I0), JP4.23
REG_0_OUT_1: IC15.3 (D1), IC33.5 (2Q), IC96.2 (I1), JP4.25
REG_0_OUT_2: IC22.3 (D1), IC33.6 (3Q), IC96.12 (I0), JP4.27
REG_0_OUT_3: IC31.3 (D1), IC33.9 (4Q), IC96.13 (I1), JP4.29
REG_0_OUT_4: IC33.12 (5Q), IC37.3 (D1), IC94.9 (I0), JP4.31
REG_0_OUT_5: IC33.15 (6Q), IC42.3 (D1), IC94.10 (I1), JP4.33
REG_0_OUT_6: IC33.16 (7Q), IC46.3 (D1), IC94.12 (I0), JP4.35
REG_0_OUT_7: IC33.19 (8Q), IC50.3 (D1), IC94.13 (I1), JP4.37
REG_1_LOAD_INPUT: IC26.11 (CLK), IC29.4 (O)
REG_1_OUT_0: IC3.2 (D2), IC26.2 (1Q)
REG_1_OUT_1: IC15.2 (D2), IC26.5 (2Q)
REG_1_OUT_2: IC22.2 (D2), IC26.6 (3Q)
REG_1_OUT_3: IC26.9 (4Q), IC31.2 (D2)
REG_1_OUT_4: IC26.12 (5Q), IC37.2 (D2)
REG_1_OUT_5: IC26.15 (6Q), IC42.2 (D2)
REG_1_OUT_6: IC26.16 (7Q), IC46.2 (D2)
REG_1_OUT_7: IC26.19 (8Q), IC50.2 (D2)
REG_2_LOAD_INPUT: IC18.11 (CLK), IC29.10 (O)
REG_2_OUT_0: IC3.1 (D3), IC18.2 (1Q)
REG_2_OUT_1: IC15.1 (D3), IC18.5 (2Q)
REG_2_OUT_2: IC18.6 (3Q), IC22.1 (D3)
REG_2_OUT_3: IC18.9 (4Q), IC31.1 (D3)
REG_2_OUT_4: IC18.12 (5Q), IC37.1 (D3)
REG_2_OUT_5: IC18.15 (6Q), IC42.1 (D3)
REG_2_OUT_6: IC18.16 (7Q), IC46.1 (D3)
REG_2_OUT_7: IC18.19 (8Q), IC50.1 (D3)
REG_3_LOAD_INPUT: IC5.11 (CLK), IC29.13 (O)
REG_3_OUT_0: IC3.15 (D4), IC5.2 (1Q)
REG_3_OUT_1: IC5.5 (2Q), IC15.15 (D4)
REG_3_OUT_2: IC5.6 (3Q), IC22.15 (D4)
REG_3_OUT_3: IC5.9 (4Q), IC31.15 (D4)
REG_3_OUT_4: IC5.12 (5Q), IC37.15 (D4)
REG_3_OUT_5: IC5.15 (6Q), IC42.15 (D4)
REG_3_OUT_6: IC5.16 (7Q), IC46.15 (D4)
REG_3_OUT_7: IC5.19 (8Q), IC50.15 (D4)
REG_TO_DBUS_H_JMP_RET: IC44.6 (I1), IC56.6 (O)
REG_TO_DBUS_L_JMP_RET: IC44.2 (I0), IC56.8 (O)
RING_CNTR_CLOCK: IC53.3 (CLK), IC53.11 (CLK), IC54.3 (CLK), IC54.11 (CLK), IC59.2 (I1), IC59.13 (I1), IC105.3 (CLK), IC105.11 (CLK), IC129.5 (I), JP4.4
SECOND_LATCH_SELECT: IC12.1 (!A!/B), IC12.13 (4B), IC65.8 (O)
SELECT_CARRY_BIT: IC70.8 (O), IC72.2 (I1), IC72.10 (I1), IC72.13 (I1), IC89.5 (I1)
SP_COUNT_DOWN: IC93.4 (DN), IC130.11 (O)
SP_COUNT_UP/WRITE_REG_TO_DBUS_SELECTOR2_PUSH: IC55.10 (I1), IC93.5 (UP), IC130.6 (O)
SP_DATA_OUT_0: IC93.3 (QA), JP2.1
SP_DATA_OUT_1: IC93.2 (QB), JP2.3
SP_DATA_OUT_2: IC93.6 (QC), JP2.5
SP_DATA_OUT_3: IC93.7 (QD), JP2.7
SP_DATA_OUT_4: IC97.3 (QA), JP2.9
SP_DATA_OUT_5: IC97.2 (QB), JP2.11
SP_DATA_OUT_6: IC97.6 (QC), JP2.13
SP_DATA_OUT_7: IC97.7 (QD), JP2.15
SP_DATA_OUT_8: IC102.3 (QA), JP2.17
SP_DATA_OUT_9: IC102.2 (QB), JP2.19
SP_DATA_OUT_10: IC102.6 (QC), JP2.21
SP_DATA_OUT_11: IC102.7 (QD), JP2.23
SP_DATA_OUT_12: IC106.3 (QA), JP2.25
SP_DATA_OUT_13: IC106.2 (QB), JP2.27
SP_DATA_OUT_14: IC106.6 (QC), JP2.29
SP_DATA_OVER/UNDERFLOW: IC106.7 (QD), JP4.18
STATE_0/CYCL_3: IC40.9 (I0), IC52.1 (I0), IC54.5 (Q), IC54.12 (D), IC99.1 (I0), IC100.4 (I0), IC100.9 (I0), IC100.12 (I0), IC130.4 (I0), JP4.30
STATE_1/CYCL_4: IC40.4 (I0), IC52.4 (I0), IC54.9 (Q), IC72.1 (I0), IC78.9 (I0), IC89.1 (I0), IC92.1 (I0), IC100.1 (I0), IC105.2 (D), IC108.1 (I0), IC126.4 (I0), IC130.9 (I0), IC130.12 (I0), JP4.32
STATE_2/CYCL_5: IC40.12 (I0), IC52.12 (I0), IC72.9 (I0), IC88.9 (I0), IC92.4 (I0), IC99.4 (I0), IC105.5 (Q), IC105.12 (D), IC126.1 (I0), JP4.34
STATE_3/CYCL_6: IC40.1 (I0), IC52.9 (I0), IC53.2 (D), IC72.12 (I0), IC105.9 (Q), IC126.9 (I0), IC126.12 (I0), JP4.36
STORE_ALU_OUTPUT: IC49.6 (O), IC101.11 (ENC)
STORE_ALU_OUTPUT/STORE_CARRY_ALU: IC49.4 (I0), IC67.9 (I), IC72.8 (O)
STORE_ALU_OUTPUT_JMP_O: IC40.11 (O), IC49.5 (I1), IC88.5 (I1), IC88.13 (I1)
STR: IC71.2 (I1), IC95.6 (O)
STR/STR_I: IC48.9 (I0), IC71.3 (O), IC100.13 (I1), IC130.10 (I1)
STR_I: IC71.1 (I0), IC95.3 (O), IC99.5 (I1)
TABLE_1_INPUT_PTR_HIGH: IC10.6 (O), IC39.5 (I0)
TABLE_1_INPUT_PTR_L: IC10.3 (O), IC39.2 (I0)
TABLE_1_INPUT_REG0: IC2.3 (O), IC29.2 (I0)
TABLE_1_INPUT_REG1: IC2.6 (O), IC29.5 (I0)
TABLE_1_INPUT_REG2: IC2.8 (O), IC29.8 (I0)
TABLE_1_INPUT_REG3: IC2.11 (O), IC29.11 (I0)
TIMER_CLOCK: IC75.5 (UP), JP4.3
TIMER_REG_0: IC4.12 (D7), IC75.3 (QA)
TIMER_REG_1: IC16.12 (D7), IC75.2 (QB)
TIMER_REG_2: IC23.12 (D7), IC75.6 (QC)
TIMER_REG_3: IC32.12 (D7), IC75.7 (QD)
TIMER_REG_4: IC38.12 (D7), IC80.3 (QA)
TIMER_REG_5: IC43.12 (D7), IC80.2 (QB)
TIMER_REG_6: IC47.12 (D7), IC80.6 (QC)
TIMER_REG_7: IC51.12 (D7), IC80.7 (QD)
TWO_BYTE_CMD: IC14.10 (O), IC89.13 (I1)
VCC: IC1.14 (VCC), IC2.14 (VCC), IC3.16 (VCC), IC4.16 (VCC), IC5.20 (VCC), IC6.14 (VCC), IC7.14 (VCC), IC8.14 (VCC), IC9.16 (VCC), IC10.14 (VCC), IC11.16 (VCC), IC12.16 (VCC), IC13.16 (VCC), IC14.14 (VCC), IC15.16 (VCC), IC16.16 (VCC), IC17.4 (DN), IC17.16 (VCC), IC18.20 (VCC), IC19.14 (VCC), IC20.14 (VCC), IC21.16 (VCC), IC22.16 (VCC), IC23.16 (VCC), IC24.14 (VCC), IC25.14 (VCC), IC26.20 (VCC), IC27.16 (VCC), IC28.14 (VCC), IC29.14 (VCC), IC30.14 (VCC), IC31.16 (VCC), IC32.16 (VCC), IC33.20 (VCC), IC34.16 (VCC), IC35.20 (VCC), IC36.20 (VCC), IC37.16 (VCC), IC38.16 (VCC), IC39.14 (VCC), IC40.14 (VCC), IC41.20 (VCC), IC42.16 (VCC), IC43.16 (VCC), IC44.14 (VCC), IC45.20 (VCC), IC46.16 (VCC), IC47.16 (VCC), IC48.14 (VCC), IC49.14 (VCC), IC50.16 (VCC), IC51.16 (VCC), IC52.14 (VCC), IC53.1 (CLR), IC53.10 (PRE), IC53.14 (VCC), IC54.4 (PRE), IC54.10 (PRE), IC54.14 (VCC), IC55.14 (VCC), IC56.14 (VCC), IC57.16 (VCC), IC58.4 (DN), IC58.16 (VCC), IC59.14 (VCC), IC60.16 (VCC), IC61.16 (VCC), IC63.14 (VCC), IC64.16 (VCC), IC65.14 (VCC), IC67.14 (VCC), IC68.14 (VCC), IC69.16 (VCC), IC70.14 (VCC), IC71.14 (VCC), IC72.14 (VCC), IC73.20 (VCC), IC74.16 (VCC), IC75.4 (DN), IC75.11 (LD), IC75.16 (VCC), IC77.14 (VCC), IC78.14 (VCC), IC79.20 (VCC), IC80.4 (DN), IC80.11 (LD), IC80.16 (VCC), IC81.20 (VCC), IC82.14 (VCC), IC83.14 (VCC), IC85.20 (VCC), IC86.14 (VCC), IC87.14 (VCC), IC88.14 (VCC), IC89.14 (VCC), IC90.14 (VCC), IC91.14 (VCC), IC92.14 (VCC), IC93.11 (LD), IC93.16 (VCC), IC94.14 (VCC), IC95.14 (VCC), IC96.14 (VCC), IC97.11 (LD), IC97.16 (VCC), IC99.14 (VCC), IC100.14 (VCC), IC101.20 (VCC), IC102.11 (LD), IC102.16 (VCC), IC103.20 (VCC), IC105.4 (PRE), IC105.10 (PRE), IC105.14 (VCC), IC106.11 (LD), IC106.16 (VCC), IC108.14 (VCC), IC112.14 (VCC), IC126.14 (VCC), IC129.14 (VCC), IC130.14 (VCC), IC131.10 (PRE), IC131.13 (CLR), IC131.14 (VCC), JP1.28, JP2.12, JP2.28, JP3.19, JP3.20, JP4.17, JP4.19, JP5.19, JP5.20
WQWJKDHSAAASDFXGHCJFDSAAS: IC40.2 (I1), IC40.5 (I1), IC40.10 (I1), IC40.13 (I1), IC59.9 (I0), IC108.6 (O), IC108.9 (I0)
WRITE_LR_L_DBUS_RET: IC65.1 (I0), IC99.3 (O)
WRITE_PC_H/WRITE_PC_L_DBUS_SAVE_LR: IC12.10 (3B), IC65.10 (I1), IC65.11 (O)
WRITE_PC_L_DBUS_JMP_O: IC40.8 (O), IC56.2 (I1)
WRITE_PC_L_DBUS_SAVE_LR: IC56.1 (I0), IC78.8 (O)
WRITE_PTR_TO_ABUS/CLR_NOT_OE/CLR_NOT_CS/FILL_REGISTER_LDR: IC68.1 (I0), IC68.5 (I1), IC96.5 (I1), IC100.8 (O)
WRITE_PTR_TO_ABUS/CLR_NOT_WE/CLR_NOT_CS_STR: IC67.3 (I), IC68.2 (I1), IC130.8 (O)
WRITE_REGB_TO_DBUS_JMP: IC1.12 (I0), IC52.11 (O)
WRITE_REG_TO_DBUS_SELECTOR2_STR: IC55.9 (I0), IC100.11 (O)

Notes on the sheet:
ProgrammCounter
InstructionRegister_HIGH
Reg0
ALU Function Selection
Opcode Nibble
MOV
Reg1
Reg2
Reg3
OpcodeStorage
To ALU input B
From ALU Output
ALU Interface
ABus Mux
Ring Counter
Memory Interface
ALU_OPERATION
LDR
To ALU input A
STR
PUSH
POP
Opcode Instruction Decoder
RAM W24129AK
FLASH W29EE011
MOVZ
Check whether reg0 is zero. Needed for the MOVZ and JMPZ instruction
Latch
Misc
SET_PTR
ALU
JMP
JMPZ
JMPC
Opcode Operand Decoder
Check if output_reg == input_reg if yes, IR needs to be applied to dbus
Switch between decode table 1 and 2
Encode it for the reg_selector
Operand byte storage for two-byte instructions
Addr15 decides whether to use RAM or FLASH

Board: 2 copper layers, 111 parts (0 on the bottom side), 464 nets, no tracks yet.
